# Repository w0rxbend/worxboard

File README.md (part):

<div align="center">

# ⌨️ worxboard

**An ErgoDox-style split keyboard, generated from one layout package.**

On-board RP2040 · ZMK wired split · a memory LCD on each half · per-key RGB · USB-C on both halves · MX hot-swap, fully assembled at JLCPCB or PCBWay · CNC aluminium case

<sub>🚧 <b>rev B is designed on four layers and its gates passed locally on 2026-11-12. Order only from a commit with a green pcb workflow. Not built.</b></sub>

    <br>

**[🌐 Live 3D viewer](https://w0rxbend.github.io/worxboard/) · [🛒 Order it](#-order-it) · [🚀 Zero to typing](#-from-zero-to-typing) · [🔧 Build guide](docs/buildguide_en.md) · [📋 BOM](docs/bom.md) · [🧾 Shopping list](docs/shopping-list.md)**<br>**[💾 Firmware](docs/firmware.md) · [🧱 Case](docs/case.md) · [📐 Design spec](docs/design.md) · [🧪 Verification](docs/verification.md)**

<sub>🖥️ Both halves in the browser 3D viewer, built from <a href="layout/build/layout.json">layout.json</a>: ErgoDox stagger, 25° thumbs, the display in the inner top slot, the tent legs. A render, not a photo, committed on 2026-11-02, before case revisions A3 to A5 and before rev B, so the case has no raised display bezel yet and the boards have no LEDs.</sub>

</div>

worxboard keeps the exact ErgoDox key positions and the 25° six-key thumb cluster. On each half, the top key of the inner column is replaced by a vertical memory LCD, an RGB LED sits under every switch, and the two halves link over TRRS with ZMK's wired split. Everything is generated from one layout package, [`layout/`](layout/): the KiCad schematics and PCBs, the build123d case, the ZMK physical layout, the docs tables and the 3D viewer. On every push to `main` and every pull request, CI rebuilds and checks the layout, the firmware, both PCBs with their order packages, and the case with its order package. The generated docs tables are checked by `just docs-check`, and the viewer is built by `just site`. Both also run in the manual `pages` workflow.

> [!WARNING]
> **Status: rev B passed its gates locally and in CI on 2026-11-12, and is tagged as the pre-release `v0.2.0-revB`; only the order-day stock check stays open.** Its PCBs moved to four layers (solid GND and VLED planes, scripted LED cells, the repo's own maze router; no Freerouting, [REVB-8](docs/deviations.md)), and the results of the final routed boards are in [verification.md](docs/verification.md#rev-b-results). Rev B puts an SK6812MINI-E RGB LED under every switch, moves the display 1.0 mm back from the C6R1 key well, folds in the pre-order review's minor points and adds a PCBWay order package beside the JLCPCB one ([deviations REVB-1 to REVB-9](docs/deviations.md#revb-rev-b-per-key-rgb-display-setback-and-review-fixes-layout-pcb-firmware-case-docs)). [verification.md](docs/verification.md) records rev A's gates **G1–G3** as passed and the rev B gates with their results. No board of either revision has been made, and nothing has been tested on hardware. Do not order assembled rev B boards until the `pcb` workflow is green on the commit you order from and the stock check has run. The frozen rev A design is [`docs/design.md`](docs/design.md), and every change from it is listed in [`docs/deviations.md`](docs/deviations.md). Read the [known open issues](#-known-open-issues) before you order.

| ⌨️ Keys | 🧠 MCU | 📟 Display | 🌈 RGB | 🔗 Split link | 🏭 Assembly | 🧱 Case |
|:-:|:-:|:-:|:-:|:-:|:-:|:-:|
| **74**, 37 per half | **RP2040** on each PCB | **160 × 68** memory LCD per half | **37** SK6812MINI-E per half, one under each switch | **115 200** baud UART over TRRS | **201** fab-assembled parts per half | **≈ 349 g** of 6061-T6 per half |

<details>
<summary>🚦 Status by part</summary>

| Part | State |
|---|---|
| 🧬 Layout (`layout/`) | ✅ **Done.** Keys, thumbs, display, LED positions and chain, jacks, holes, outline, zones and the GPIO map; checked by `just layout-check` |
| 🟩 PCB (`pcb/`) | ✅ **Designed (rev B, four layers). Gates passed locally and in CI; the stock check is open until the order day.** Both halves are generated in KiCad 10, with the per-key RGB chain, the VLED switch U6 and the data buffer U7, on F.Cu / GND plane / VLED plane / B.Cu. The gates of the final routed boards and their order packages in [`pcb/production/`](pcb/production/) are recorded in [verification.md](docs/verification.md#rev-b-results). The pipeline stops on an ERC error, a netlist mismatch (the RGB chain included), a DRC violation, an unconnected item or a parity issue, and on a failed scripted check: the USB pair, crystal, decoupling, U1 ground return and GND links, via-in-pad, J1 pin-in-paste, outline, and each LED in its switch window. |
| 💾 Firmware (`firmware/`, `zephyr/`, `build.yaml`) | 🔨 **Builds.** All six `build.yaml` rows build locally and in CI: left central, right peripheral, two role-swap rows and two RP2350A rows. Both screens are laid out portrait for the upright display. The LED chains run as ZMK underglow, capped at 8 % brightness. Nothing has run on hardware. |
| 🧱 Case and plates (`case/`, `plates/`) | ✅ **Orderable.** Every case check passes, and so does JLCCNC's internal-corner rule. `just fitcheck` reports 0 mm³ of interference against both PCB STEPs plus the layout envelopes. The JLCCNC / JLC3DP package for case revision A5 (with PCBWay notes) is committed in [`case/production/`](case/production/README.md). Nothing has been printed or machined. |
| 📚 Docs and microsite (`docs/`, `site/`) | ✅ **Done.** The turnkey ordering guides for JLCPCB and PCBWay, shopping list, build guide, generated BOM, pinout and matrix, and the electrical, case, legs and firmware docs. The site is a product page with the 3D viewer and a build guide rendered from these docs. |
| 🧪 Gates and release | ✅ **Rev A and rev B passed. Rev B is the pre-release `v0.2.0-revB`.** [`docs/verification.md`](docs/verification.md) records rev A's integration tests (111 passed), CI, order-package checks and gates G1–G3, and the rev B gate results of 2026-11-12. [`release.yml`](.github/workflows/release.yml) publishes the committed order packages, the firmware and the case files on a `v*` tag. The tag `v0.1.0-revA` points at the rev A commit, `v0.2.0-revB` at rev B. |
| 🛠️ Hardware | ⏳ **Not built.** What only a real board can confirm is [listed](docs/verification.md#not-verified-until-a-board-is-built). |

</details>

## 🧭 Contents

| 👀 See it | 🛠️ Make it | 📖 Know it |
|---|---|---|
| [📸 Gallery](#-gallery) | [🚀 From zero to typing](#-from-zero-to-typing) | [🤖 Generated, not drawn](#-generated-not-drawn) |
| [✨ Features](#-features) | [🛒 Order it](#-order-it) | [🐛 Known open issues](#-known-open-issues) |
| [📊 Specs](#-specs) | [🔧 Build it](#-build-it) | [🔭 Future work](#-future-work) |
| [📐 Layout and matrix](#-layout-and-matrix) | [💾 Firmware](#-firmware) | [🌳 Repository layout](#-repository-layout) |
| [🌐 Spin it in your browser](#-spin-it-in-your-browser) | [🧱 Case](#-case) | [📚 Documentation](#-documentation) |
| | [🧰 Build from source](#-build-from-source) | [🙏 Credits](#-credits) |
| | [📦 Get the files](#-get-the-files) | [📜 License](#-license) |

## 📸 Gallery

> [!NOTE]
> Every image in this README is a render, a CAD drawing or a screenshot. No photos exist yet, because no board has been built. The PCB renders and the CPL proofs were regenerated from the rev B boards on 2026-11-12, and the case renders show case revision A5. The two viewer images were captured from the microsite's 3D viewer on 2026-11-12: they show rev B in the case of revision A5, with the LEDs lit. KiCad has no 3D model for the USB-C, the TRRS jack or the hot-swap sockets, so the PCB renders show only their footprints.

<table>
<tr><td align="center" width="50%"><br><sub>💥 Right half exploded in the viewer: tray, PCB, printed spacer, top shell, switches, keycaps</sub></td><td align="center" width="50%"><br><sub>🦵 Closed right-half case with its three custom tent legs (CAD render)</sub></td></tr>
<tr><td align="center"><br><sub>🟩 Left PCB, top (rev B): RP2040, flash, USB-C J1, BOOT/RESET, JP1 (“cut = split power”), display socket J3, TRRS jack J2 on the inner bump</sub></td><td align="center"><br><sub>🟩 Right PCB, top (rev B): mirrored, same netlist; both boards print DO NOT HOT-PLUG TRRS and HOST → LEFT by J2</sub></td></tr>
<tr><td align="center"><br><sub>🟩 Left PCB, bottom (rev B): 37 hot-swap socket footprints and 37 diodes; rev B adds an LED and its cap at every key</sub></td><td align="center"><br><sub>🟩 Right PCB, bottom (rev B): 37 socket footprints and 37 diodes, all fitted by the fab</sub></td></tr>
<tr><td align="center" colspan="2"><br><sub>🧱 Both CNC top shells: the plate is milled into the key well, with 2u stabiliser cut-outs and a display window on each half</sub></td></tr>
</table>

## ✨ Features

<table>
<tr><td width="33%" valign="top">

**📐 Exact ErgoDox layout**<br>The switch centres, the column stagger and the 25° thumb cluster come from the original ErgoDox PCB. The thumb keys match it within 0.002 mm, and the main keys match the spec table within 0.0001 mm. 37 keys per half, 74 in total.

</td><td width="33%" valign="top">

**📟 A display on each half**<br>A Sharp LS011B7DH03 memory LCD (160 × 68) on a nice!view-class module sits where the inner top key was, behind a window in the case. The left half shows the ZMK status screen. The right half shows a custom lock-indicator screen.

</td><td width="33%" valign="top">

**🧠 On-board RP2040**<br>There is no controller daughterboard. The support circuit is derived from the [Corne v4.1](https://github.com/foostan/crkbd): QSPI flash, a 12 MHz crystal, an LDO and ESD arrays. JLCPCB or PCBWay fits all 201 parts per half, on both sides.

</td></tr>
<tr><td valign="top">

**🔌 USB-C on both halves**<br>Plug the host into the **left** half. The right USB-C gives power and UF2 flashing. Schottky diodes let you plug in both at once without back-feeding either host.

</td><td valign="top">

**🔗 A careful wired split**<br>ZMK `zmk,wired-split` runs on UART0 at 115 200 baud over a straight TRRS cable. The tip carries only 1 kΩ-limited data. Power sits on Ring2 behind a 250 mA polyfuse, and solder jumper JP1 turns cable power off.

</td><td valign="top">

**🔥 Hot-swap, no PCB soldering**<br>MX hot-swap sockets of the CPG151101S11 type sit on the bottom, with 2u plate-mount stabilisers on two thumb keys per half. The fab fits every PCB part, display socket and LEDs included; you solder only the displays' header pins (and any J1 shell leg that arrives bare).

</td></tr>
<tr><td valign="top">

**🧱 CNC aluminium case**<br>Each half has a 6061-T6 top shell with the 1.5 mm plate milled into it, a 6061-T6 tray and a printed 3 mm spacer. The finish is bead blast plus anodize. A raised bezel covers the display.

</td><td valign="top">

**🦵 Tent legs like the EZ**<br>Each half has three mounts at the stock ErgoDox EZ positions. Every mount takes one custom aluminium leg with a TPU foot cap, clamped by an M3 × 12 collarless thumbscrew and a friction washer.

</td><td valign="top">

**🤖 Generated, not drawn**<br>The schematic, placement, routing, DRC, fab files, case, physical layout and docs tables are all scripts. The PCB stages run headless in a digest-pinned KiCad container, with the repo's own router and seeded ids, so a rebuild gives byte-identical boards.

</td></tr>
<tr><td colspan="3" valign="top">

**🌈 Per-key RGB (rev B)**<br>An SK6812MINI-E sits under every switch, 37 per half, reverse-mounted in a cutout so it shines up through the switch's LED window on the south side (towards you); the fab places them with everything else. ZMK drives each half's chain as an underglow strip: whole-board effects (solid, breathe, spectrum, swirl), toggle, hue and brightness on the layer-1 thumbs, and the left half relays them to the right. There are no per-key or per-layer colours. A load switch keeps the LEDs unpowered until the firmware turns them on, and brightness is capped at 8 % so that one cable can feed both halves. None of it has run on hardware yet.

</td></tr>
</table>

## 📊 Specs

| Spec | rev B |
|---|---|
| ⌨️ **Keys** | 74 (37 per half). Each half has a 6 × 7 `col2row` matrix; ZMK sees one 6 × 14 transform |
| 🧠 **Controller** | RP2040 (QFN-56) per half, with W25Q128JVSIQ 16 MB QSPI flash and a 12 MHz crystal |
| 📟 **Display** | Sharp LS011B7DH03, 160 × 68 memory LCD on a nice!view-class module, driven over PIO1 SPI at 1 MHz. Rev B sets the module 1.0 mm back, so its far end stops about 0.2–0.3 mm short of the C6R1 key well (36 mm module plus its V-cut) |
| 🌈 **RGB** | 37 SK6812MINI-E per half, reverse-mounted on the bottom under each switch, facing south. One chain per half: GP22 through a buffer (U7) on PIO0; VLED switched from VSYS by U6 on GP23, limited to 0.45 A. ZMK underglow effects, brightness capped at 8 % |
| 🔗 **Split link** | 3.5 mm TRRS, ZMK wired split on UART0 at 115 200 baud, full duplex |
| 🔌 **USB** | USB-C 2.0 full speed on both halves (HRO TYPE-C-31-M-12); the host goes on the left |
| 🟩 **PCB** | 4 layers (signal, GND plane, VLED plane, signal), 1.6 mm FR4, 1 oz outer / 0.5 oz inner copper, ENIG, 182.84 × 158.75 mm per half. The fab places 201 parts per half: 53 on top, and 148 on the bottom (37 sockets, 37 diodes, 37 LEDs and their 37 caps) |
| 🎹 **Switches** | 74 MX-compatible plate-mount switches, 3- or 5-pin, in hot-swap sockets; 4 × 2u plate-mount stabilisers |
| 💾 **Firmware** | ZMK, HWMv2 board `worxbend/worxboard`, pinned at `4dd95d78`; ZMK Studio on the left central |
| 🧱 **Case** | 3 parts per half (CNC top and tray, printed spacer); 192.4 × 165.6 × 17.6 mm, 19.6 mm at the display bezel; about 349 g per half |
| 🦵 **Legs** | 3 per half, held by M3 × 12 DIN 653 thumbscrews with friction washers |

<details>
<summary>🔬 Full specs: key parts, power path, TRRS contacts, GPIO map</summary>

**🧩 Key parts per half** (the full generated table is in [docs/bom.md](docs/bom.md)):

| Ref | Part | LCSC | Ref | Part | LCSC |
|---|---|---|---|---|---|
| U1 | RP2040, QFN-56 | [C2040](https://jlcpcb.com/partdetail/C2040) | U2 | W25Q128JVSIQ, 16 MB QSPI flash | [C97521](https://jlcpcb.com/partdetail/C97521) |
| Y1 | 12 MHz 3225 crystal, YXC XL2EL89CRI-111YLC-12M | [C49304726](https://jlcpcb.com/partdetail/C49304726) | U3 | AP2112K-3.3, 600 mA LDO | [C51118](https://jlcpcb.com/partdetail/C51118) |
| U4, U5 | USBLC6-2SC6 ESD arrays (USB, TRRS) | [C7519](https://jlcpcb.com/partdetail/C7519) | D1 | B5819W, 1 A Schottky | [C8598](https://jlcpcb.com/partdetail/C8598) |
| F1 | nSMD025-24V PTC, 250 mA hold | [C70069](https://jlcpcb.com/partdetail/C70069) | J1 | HRO TYPE-C-31-M-12 USB-C receptacle | [C165948](https://jlcpcb.com/partdetail/C165948) |
| J2 | PJ-320D-4A TRRS jack, SMD | [C95562](https://jlcpcb.com/partdetail/C95562) | J3 | 1×5 2.54 mm female socket, 5.0 mm tall (the only through-hole part) | [C27985230](https://jlcpcb.com/partdetail/C27985230) |
| SW1, SW2 | TS-1088R tact switches (BOOT, RESET) | [C455280](https://jlcpcb.com/partdetail/C455280) | SK101–SK137 | MX hot-swap socket, HanElectricity CPG151101S11-16 | [C41430893](https://jlcpcb.com/partdetail/C41430893) |
| D101–D137 | 1N4148W matrix diodes | [C81598](https://jlcpcb.com/partdetail/C81598) | LED101–LED137 | SK6812MINI-E RGB LED, reverse mount (rev B) | [C5149201](https://jlcpcb.com/partdetail/C5149201) |
| U6 | SY6280AAC load switch, VSYS → VLED (rev B) | [C55136](https://jlcpcb.com/partdetail/C55136) | U7 | SN74LV1T34DBVR buffer, GP22 → LED101 (rev B) | [C100024](https://jlcpcb.com/partdetail/C100024) |
| C1–C3 | 10 µF 0603 10 V X5R (rev B; was 0402 6.3 V) | [C19702](https://jlcpcb.com/partdetail/C19702) |  |  |  |

`design.py` fits 201 parts per half with 26 LCSC numbers; each side's [order README](pcb/production/left/README.md) gives the BOM and CPL line counts. The retired parts C2803348 (socket), C113767 (flash), C91749 (crystal) and C15525 (rev A's 0402 10 µF) fail `stock.py` and `netcmp.py` if they come back.

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
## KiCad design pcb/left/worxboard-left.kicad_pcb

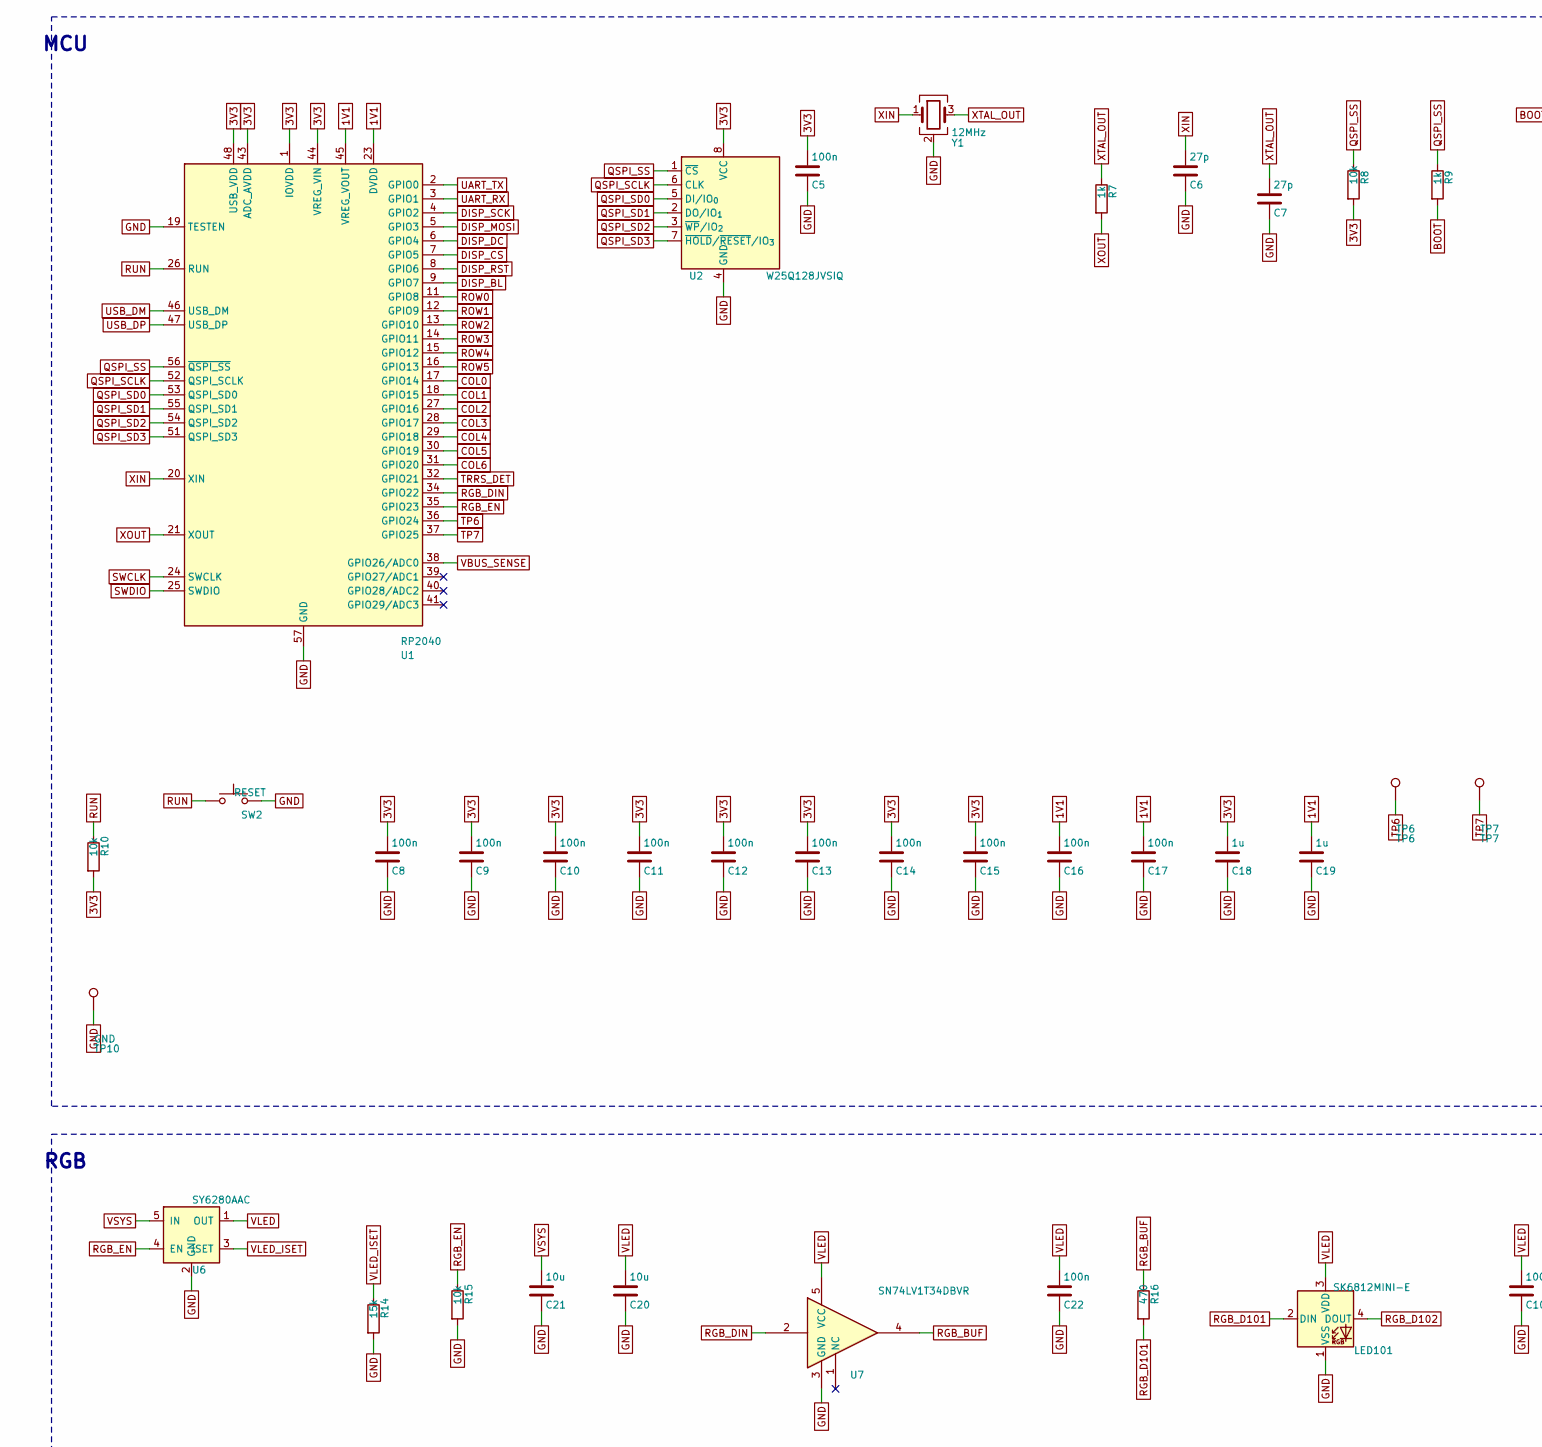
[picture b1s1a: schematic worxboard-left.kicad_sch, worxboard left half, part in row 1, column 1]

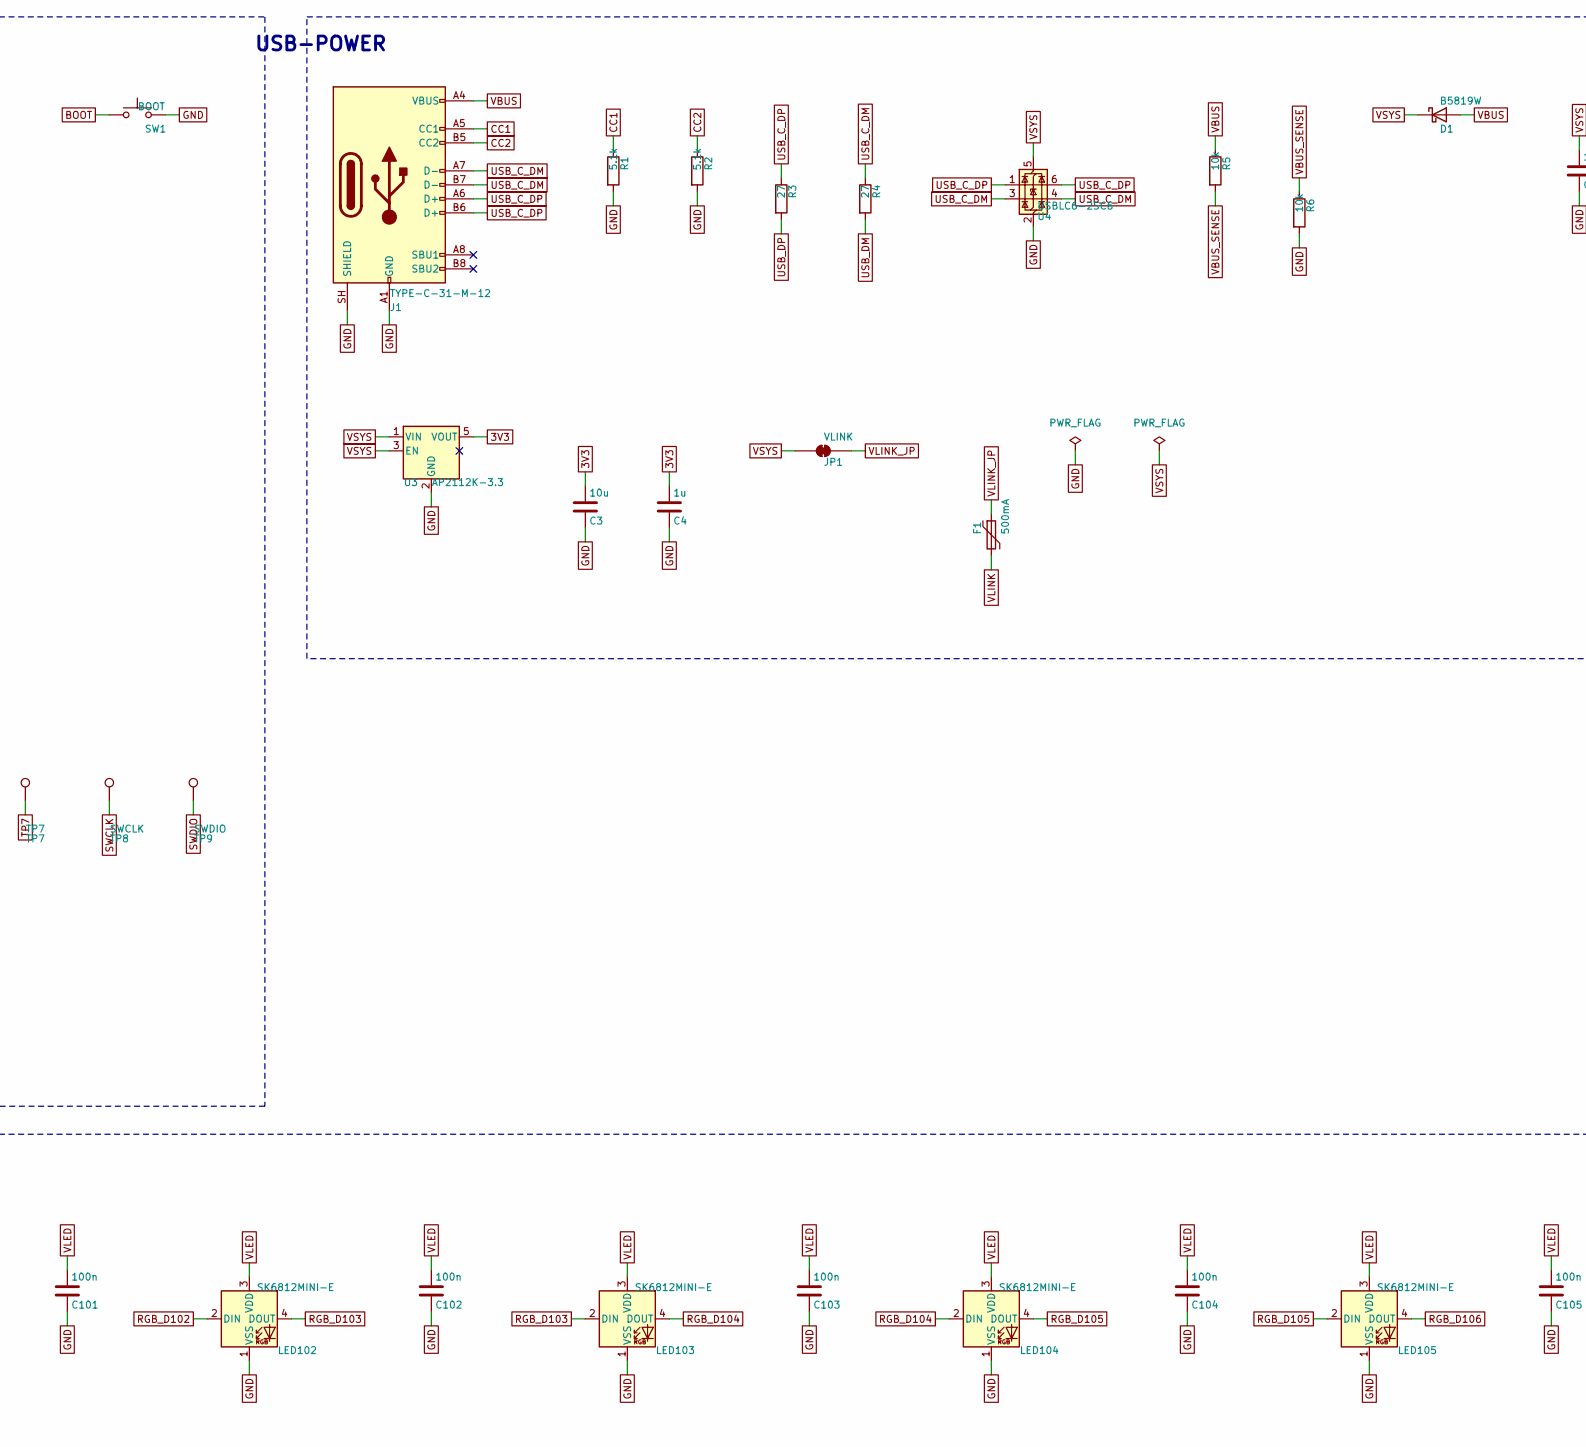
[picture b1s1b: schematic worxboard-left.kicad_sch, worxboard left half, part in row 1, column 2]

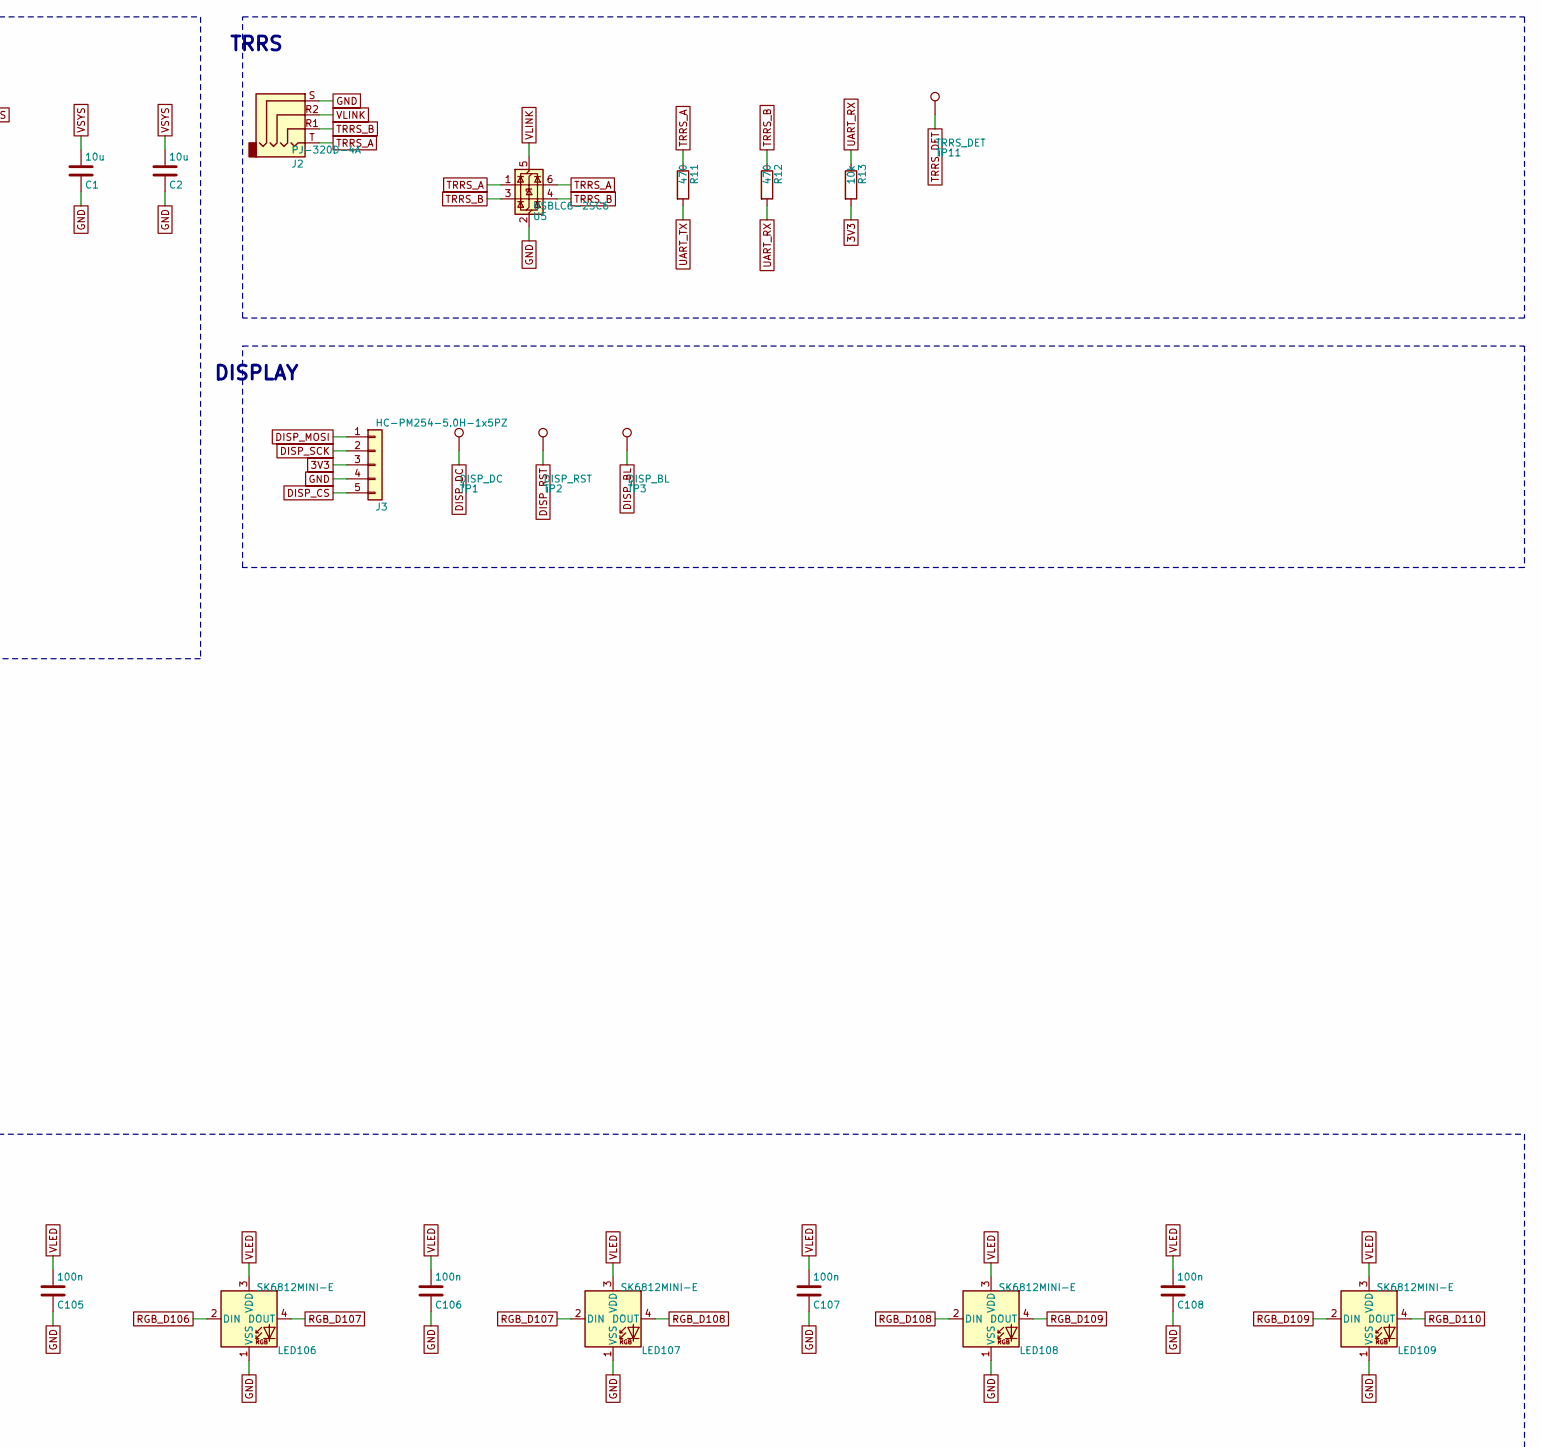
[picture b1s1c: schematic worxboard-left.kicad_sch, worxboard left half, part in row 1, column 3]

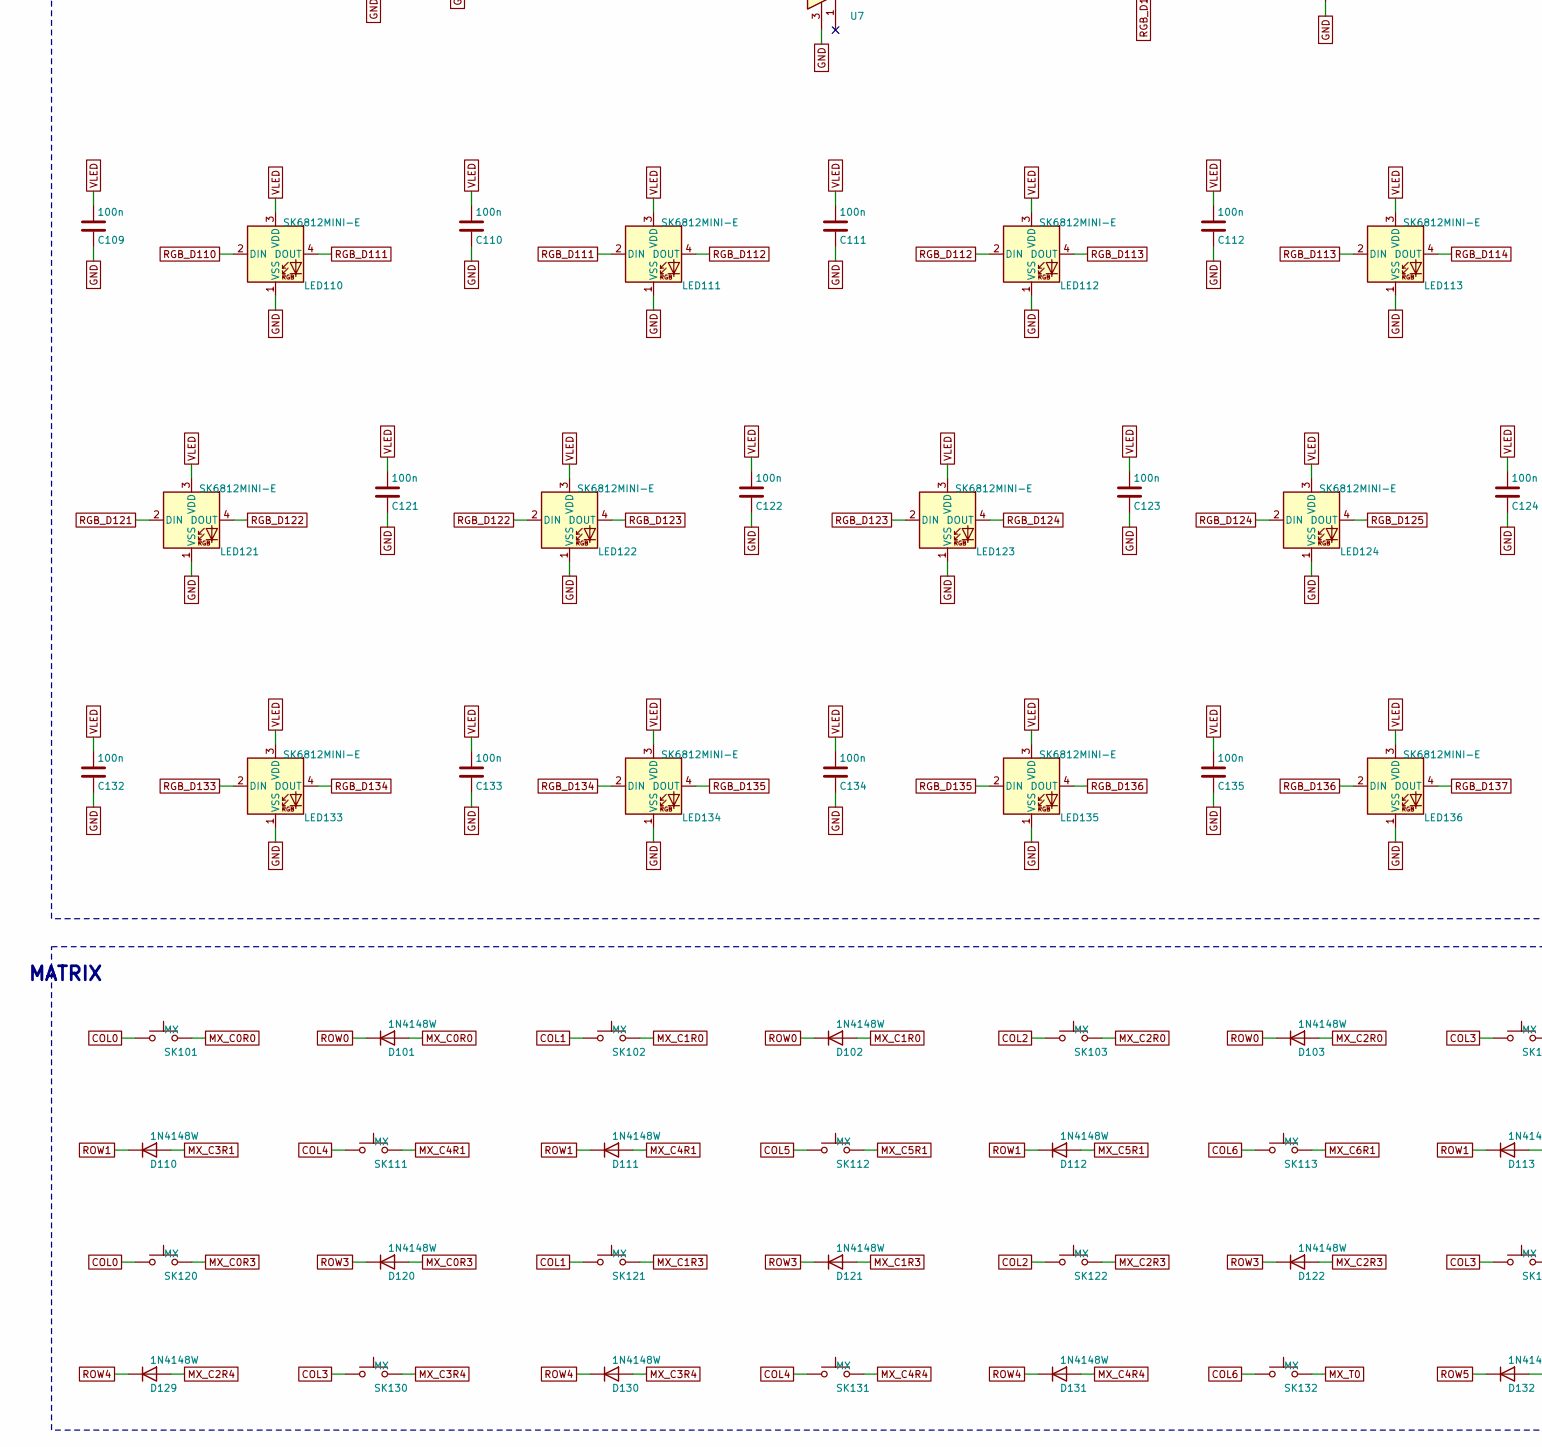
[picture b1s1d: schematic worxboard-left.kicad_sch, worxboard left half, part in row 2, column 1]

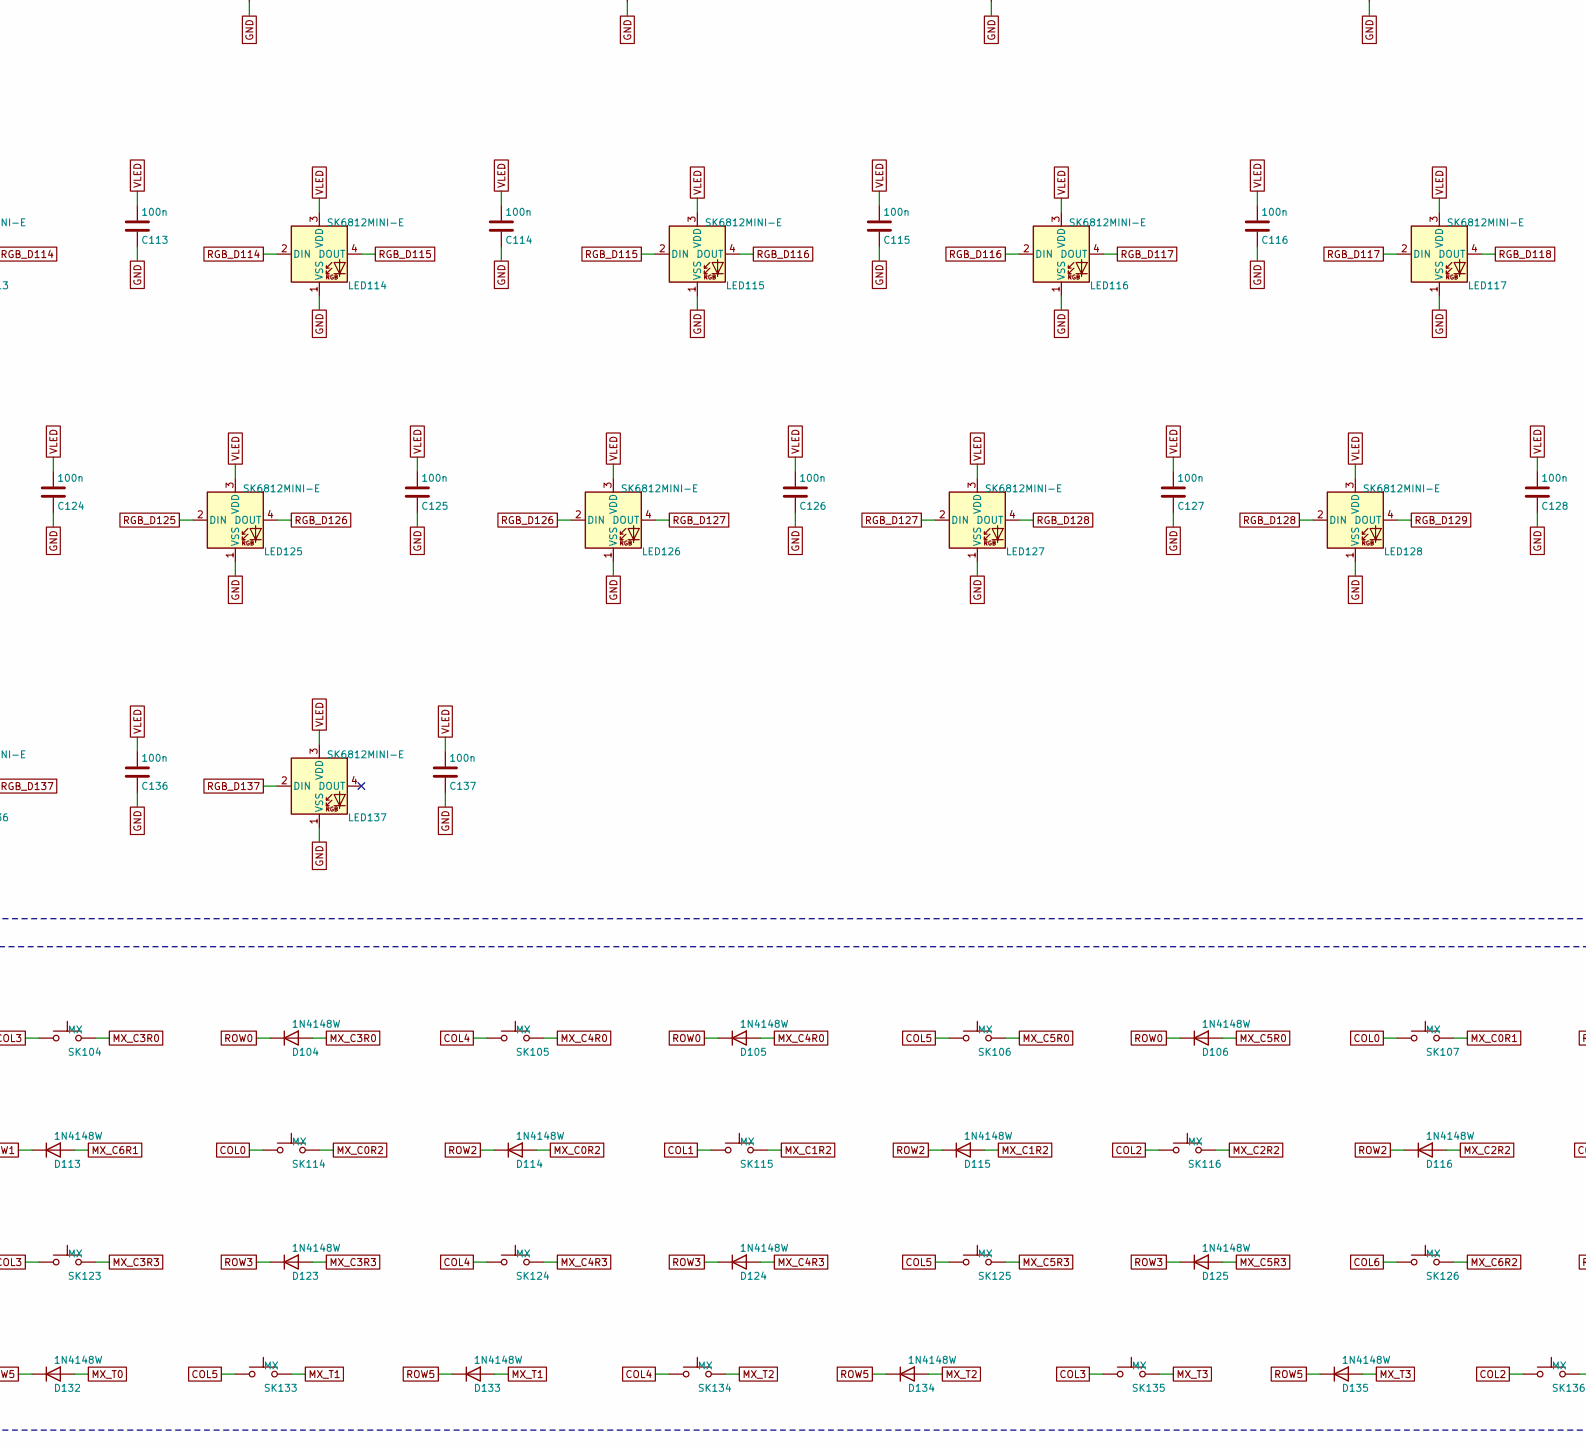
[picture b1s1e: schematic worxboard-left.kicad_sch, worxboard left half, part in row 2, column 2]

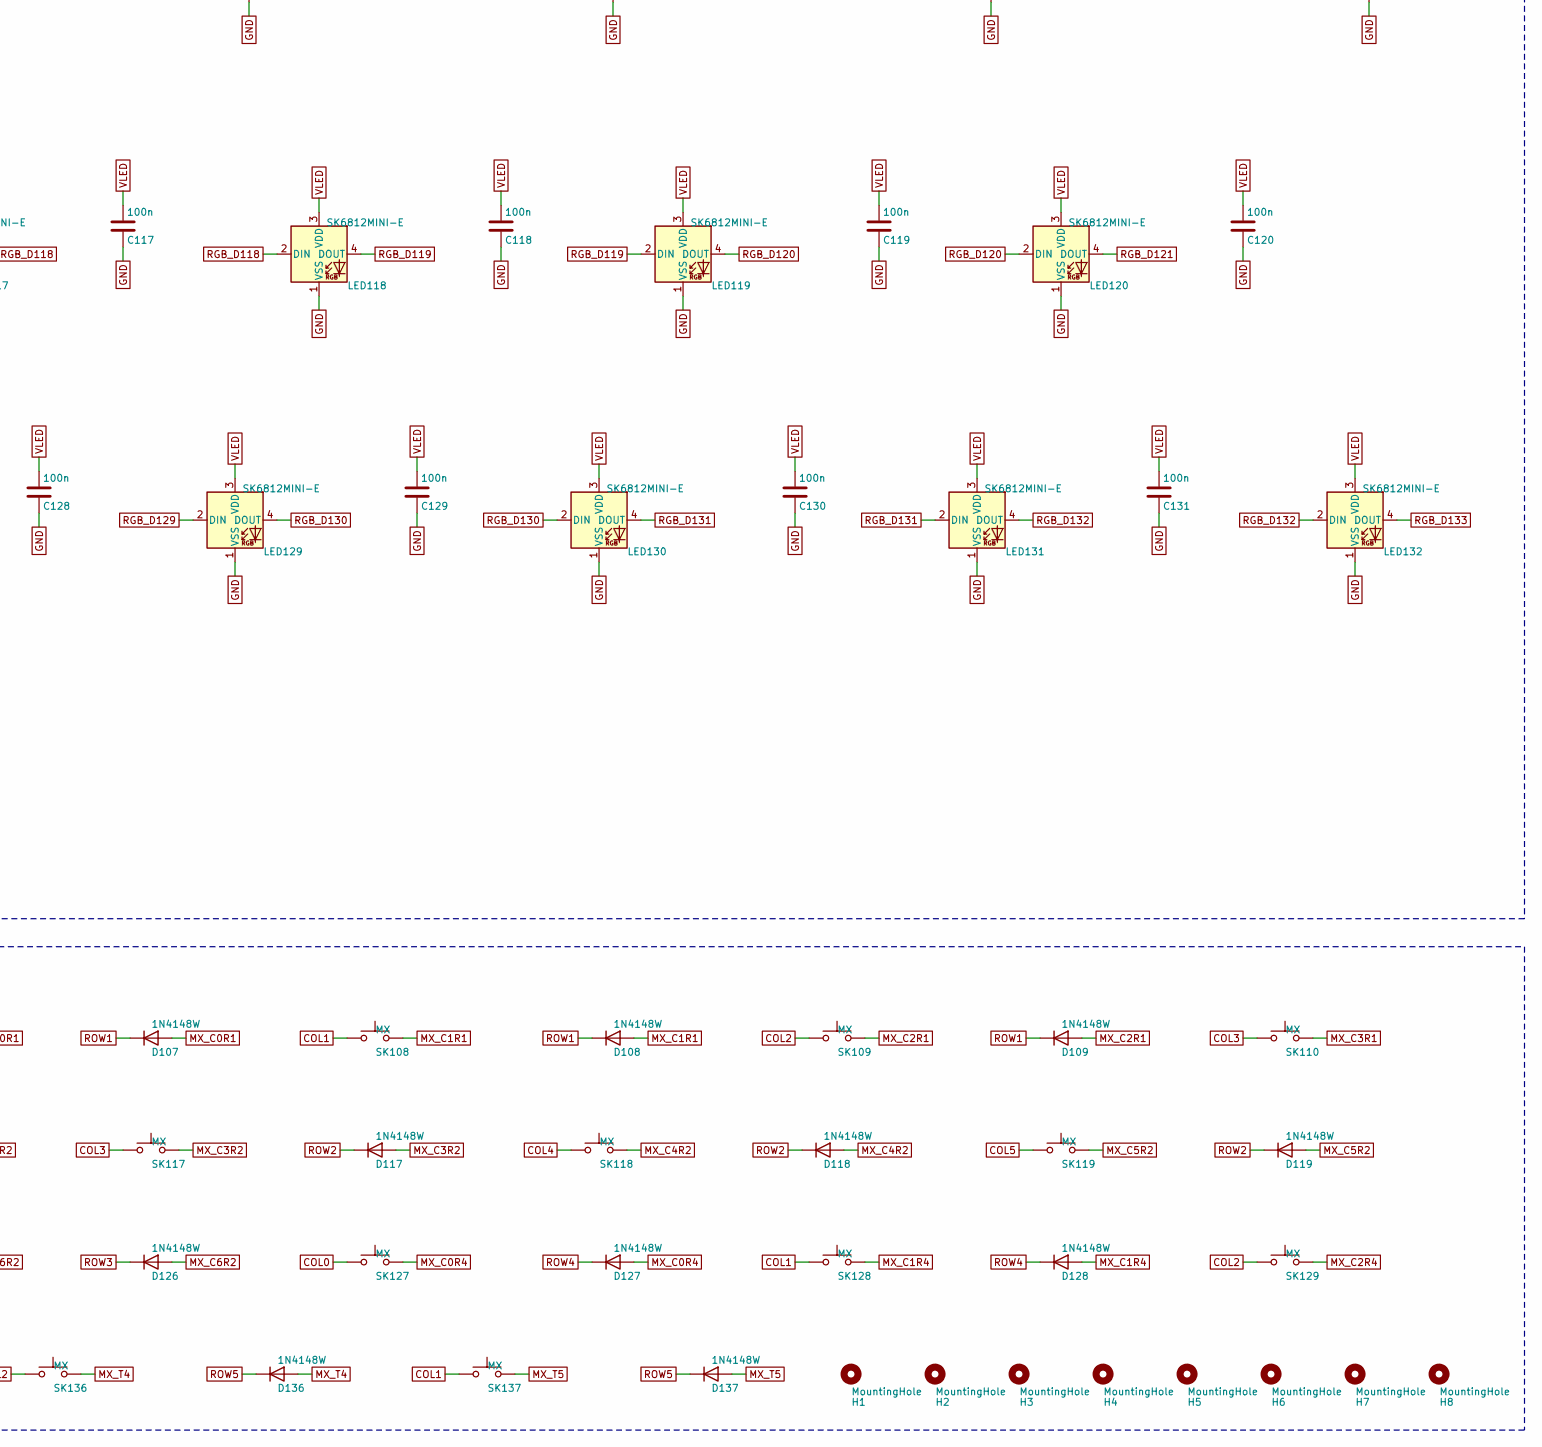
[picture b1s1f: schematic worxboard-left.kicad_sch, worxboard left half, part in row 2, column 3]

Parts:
C1, C2, C3, C20, C21: 10u; C_0603_1608Metric; LCSC C19702
C4, C18, C19: 1u; C_0402_1005Metric; LCSC C52923
C5, C8, C9, C10, C11, C12, C13, C14, C15, C16, C17, C22, C101, C102, C103, C104, C105, C106, C107, C108, C109, C110, C111, C112, C113, C114, C115, C116, C117, C118, C119, C120, C121, C122, C123, C124, C125, C126, C127, C128, C129, C130, C131, C132, C133, C134, C135, C136, C137: 100n; C_0402_1005Metric; LCSC C1525
C6, C7: 27p; C_0402_1005Metric; LCSC C1557
D1: B5819W; D_SOD-123; LCSC C8598
D101, D102, D103, D104, D105, D106, D107, D108, D109, D110, D111, D112, D113, D114, D115, D116, D117, D118, D119, D120, D121, D122, D123, D124, D125, D126, D127, D128, D129, D130, D131, D132, D133, D134, D135, D136, D137: 1N4148W; D_SOD-123; LCSC C81598
F1: 500mA; Fuse_1206_3216Metric; LCSC C70076
H1, H2, H3, H4, H5, H6, H7, H8: MountingHole; MountingHole_2.7mm_M2.5
J1: TYPE-C-31-M-12; USB_C_Receptacle_HRO_TYPE-C-31-M-12; LCSC C165948
J2: PJ-320D-4A; Jack_3.5mm_PJ320D_Horizontal; LCSC C95562
J3: HC-PM254-5.0H-1x5PZ; PinSocket_1x05_P2.54mm_Vertical_H5.0mm; LCSC C27985230
JP1: VLINK; SolderJumper-2_P1.3mm_Bridged_RoundedPad1.0x1.5mm
LED101, LED102, LED103, LED104, LED105, LED106, LED107, LED108, LED109, LED110, LED111, LED112, LED113, LED114, LED115, LED116, LED117, LED118, LED119, LED120, LED121, LED122, LED123, LED124, LED125, LED126, LED127, LED128, LED129, LED130, LED131, LED132, LED133, LED134, LED135, LED136, LED137: SK6812MINI-E; LED_SK6812MINI-E_ReverseMount; LCSC C5149201
R1, R2: 5.1k; R_0402_1005Metric; LCSC C25905
R3, R4: 27; R_0402_1005Metric; LCSC C2909343
R5, R6, R8, R10, R13, R15: 10k; R_0402_1005Metric; LCSC C25744
R7, R9: 1k; R_0402_1005Metric; LCSC C11702
R11, R12, R16: 470; R_0402_1005Metric; LCSC C25117
R14: 15k; R_0402_1005Metric; LCSC C25756
SK101, SK102, SK103, SK104, SK105, SK106, SK107, SK108, SK109, SK110, SK111, SK112, SK113, SK114, SK115, SK116, SK117, SK118, SK119, SK120, SK121, SK122, SK123, SK124, SK125, SK126, SK127, SK128, SK129, SK130, SK131, SK132, SK133, SK134, SK135, SK136, SK137: MX; SW_MX_Hotswap_Kailh; LCSC C41430893
SW1: BOOT; SW_SPST_TS-1088-xR020; LCSC C455280
SW2: RESET; SW_SPST_TS-1088-xR020; LCSC C455280
TP1: DISP_DC; TestPoint_Pad_D1.0mm
TP2: DISP_RST; TestPoint_Pad_D1.0mm
TP3: DISP_BL; TestPoint_Pad_D1.0mm
TP6: TP6; TestPoint_Pad_D1.0mm
TP7: TP7; TestPoint_Pad_D1.0mm
TP8: SWCLK; TestPoint_Pad_D1.0mm
TP9: SWDIO; TestPoint_Pad_D1.0mm
TP10: GND; TestPoint_Pad_D1.0mm
TP11: TRRS_DET; TestPoint_Pad_D1.0mm
U1: RP2040; QFN-56-1EP_7x7mm_P0.4mm_EP3.2x3.2mm; LCSC C2040
U2: W25Q128JVSIQ; SOIC-8_5.3x5.3mm_P1.27mm; LCSC C97521
U3: AP2112K-3.3; SOT-23-5; LCSC C51118
U4, U5: USBLC6-2SC6; SOT-23-6; LCSC C7519
U6: SY6280AAC; SOT-23-5; LCSC C55136
U7: SN74LV1T34DBVR; SOT-23-5; LCSC C100024
Y1: 12MHz; Crystal_SMD_3225-4Pin_3.2x2.5mm; LCSC C49304726

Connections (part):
1V1: C16.1, C17.1, C19.1, U1.23 (DVDD), U1.45 (VREG_VOUT), U1.50 (DVDD)
3V3: C3.1, C4.1, C5.1, C8.1, C9.1, C10.1, C11.1, C12.1, C13.1, C14.1, C15.1, C18.1, J3.3, R8.2, R10.2, R13.2, U1.1 (IOVDD), U1.10 (IOVDD), U1.22 (IOVDD), U1.33 (IOVDD), U1.42 (IOVDD), U1.43 (ADC_AVDD), U1.44 (VREG_VIN), U1.48 (USB_VDD), U1.49 (IOVDD), U2.8 (VCC), U3.5 (VOUT)
BOOT: R9.2, SW1.1
CC1: J1.A5 (CC1), R1.1
CC2: J1.B5 (CC2), R2.1
COL0: SK101.1, SK107.1, SK114.1, SK120.1, SK127.1, U1.17 (GPIO14)
COL1: SK102.1, SK108.1, SK115.1, SK121.1, SK128.1, SK137.1, U1.18 (GPIO15)
COL2: SK103.1, SK109.1, SK116.1, SK122.1, SK129.1, SK136.1, U1.27 (GPIO16)
COL3: SK104.1, SK110.1, SK117.1, SK123.1, SK130.1, SK135.1, U1.28 (GPIO17)
COL4: SK105.1, SK111.1, SK118.1, SK124.1, SK131.1, SK134.1, U1.29 (GPIO18)
COL5: SK106.1, SK112.1, SK119.1, SK125.1, SK133.1, U1.30 (GPIO19)
COL6: SK113.1, SK126.1, SK132.1, U1.31 (GPIO20)
DISP_BL: TP3.1, U1.9 (GPIO7)
DISP_CS: J3.5, U1.7 (GPIO5)
DISP_DC: TP1.1, U1.6 (GPIO4)
DISP_MOSI: J3.1, U1.5 (GPIO3)
DISP_RST: TP2.1, U1.8 (GPIO6)
DISP_SCK: J3.2, U1.4 (GPIO2)
GND: C1.2, C2.2, C3.2, C4.2, C5.2, C6.2, C7.2, C8.2, C9.2, C10.2, C11.2, C12.2, C13.2, C14.2, C15.2, C16.2, C17.2, C18.2, C19.2, C20.2, C21.2, C22.2, C101.2, C102.2, C103.2, C104.2, C105.2, C106.2, C107.2, C108.2, C109.2, C110.2, C111.2, C112.2, C113.2, C114.2, C115.2, C116.2, C117.2, C118.2, C119.2, C120.2, C121.2, C122.2, C123.2, C124.2, C125.2, C126.2, C127.2, C128.2, C129.2, C130.2, C131.2, C132.2, C133.2, C134.2, C135.2, C136.2, C137.2, J1.A1 (GND), J1.A12 (GND), J1.B1 (GND), J1.B12 (GND), J1.SH (SHIELD), J2.S, J3.4, LED101.1 (VSS), LED102.1 (VSS), LED103.1 (VSS), LED104.1 (VSS), LED105.1 (VSS), LED106.1 (VSS), LED107.1 (VSS), LED108.1 (VSS), LED109.1 (VSS), LED110.1 (VSS), LED111.1 (VSS), LED112.1 (VSS), LED113.1 (VSS), LED114.1 (VSS), LED115.1 (VSS), LED116.1 (VSS), LED117.1 (VSS), LED118.1 (VSS)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
MX_C0R0: D101.2 (A), SK101.2
MX_C0R1: D107.2 (A), SK107.2
MX_C0R2: D114.2 (A), SK114.2
MX_C0R3: D120.2 (A), SK120.2
MX_C0R4: D127.2 (A), SK127.2
MX_C1R0: D102.2 (A), SK102.2
MX_C1R1: D108.2 (A), SK108.2
MX_C1R2: D115.2 (A), SK115.2
MX_C1R3: D121.2 (A), SK121.2
MX_C1R4: D128.2 (A), SK128.2
MX_C2R0: D103.2 (A), SK103.2
MX_C2R1: D109.2 (A), SK109.2
MX_C2R2: D116.2 (A), SK116.2
MX_C2R3: D122.2 (A), SK122.2
MX_C2R4: D129.2 (A), SK129.2
MX_C3R0: D104.2 (A), SK104.2
MX_C3R1: D110.2 (A), SK110.2
MX_C3R2: D117.2 (A), SK117.2
MX_C3R3: D123.2 (A), SK123.2
MX_C3R4: D130.2 (A), SK130.2
MX_C4R0: D105.2 (A), SK105.2
MX_C4R1: D111.2 (A), SK111.2
MX_C4R2: D118.2 (A), SK118.2
MX_C4R3: D124.2 (A), SK124.2
MX_C4R4: D131.2 (A), SK131.2
MX_C5R0: D106.2 (A), SK106.2
MX_C5R1: D112.2 (A), SK112.2
MX_C5R2: D119.2 (A), SK119.2
MX_C5R3: D125.2 (A), SK125.2
MX_C6R1: D113.2 (A), SK113.2
MX_C6R2: D126.2 (A), SK126.2
MX_T0: D132.2 (A), SK132.2
MX_T1: D133.2 (A), SK133.2
MX_T2: D134.2 (A), SK134.2
MX_T3: D135.2 (A), SK135.2
MX_T4: D136.2 (A), SK136.2
MX_T5: D137.2 (A), SK137.2
QSPI_SCLK: U1.52 (QSPI_SCLK), U2.6 (CLK)
QSPI_SD0: U1.53 (QSPI_SD0), U2.5 (DI/IO_{0})
QSPI_SD1: U1.55 (QSPI_SD1), U2.2 (DO/IO_{1})
QSPI_SD2: U1.54 (QSPI_SD2), U2.3 (~WP/IO_{2})
QSPI_SD3: U1.51 (QSPI_SD3), U2.7 (~HOLD/~RESET/IO_{3})
QSPI_SS: R8.1, R9.1, U1.56 (~QSPI_SS), U2.1 (~CS)
RGB_BUF: R16.1, U7.4
RGB_D101: LED101.2 (DIN), R16.2
RGB_D102: LED101.4 (DOUT), LED102.2 (DIN)
RGB_D103: LED102.4 (DOUT), LED103.2 (DIN)
RGB_D104: LED103.4 (DOUT), LED104.2 (DIN)
RGB_D105: LED104.4 (DOUT), LED105.2 (DIN)
RGB_D106: LED105.4 (DOUT), LED106.2 (DIN)
RGB_D107: LED106.4 (DOUT), LED107.2 (DIN)
RGB_D108: LED107.4 (DOUT), LED108.2 (DIN)
RGB_D109: LED108.4 (DOUT), LED109.2 (DIN)
RGB_D110: LED109.4 (DOUT), LED110.2 (DIN)
RGB_D111: LED110.4 (DOUT), LED111.2 (DIN)
RGB_D112: LED111.4 (DOUT), LED112.2 (DIN)
RGB_D113: LED112.4 (DOUT), LED113.2 (DIN)
RGB_D114: LED113.4 (DOUT), LED114.2 (DIN)
RGB_D115: LED114.4 (DOUT), LED115.2 (DIN)
RGB_D116: LED115.4 (DOUT), LED116.2 (DIN)
RGB_D117: LED116.4 (DOUT), LED117.2 (DIN)
RGB_D118: LED117.4 (DOUT), LED118.2 (DIN)
RGB_D119: LED118.4 (DOUT), LED119.2 (DIN)
RGB_D120: LED119.4 (DOUT), LED120.2 (DIN)
RGB_D121: LED120.4 (DOUT), LED121.2 (DIN)
RGB_D122: LED121.4 (DOUT), LED122.2 (DIN)
RGB_D123: LED122.4 (DOUT), LED123.2 (DIN)
RGB_D124: LED123.4 (DOUT), LED124.2 (DIN)
RGB_D125: LED124.4 (DOUT), LED125.2 (DIN)
RGB_D126: LED125.4 (DOUT), LED126.2 (DIN)
RGB_D127: LED126.4 (DOUT), LED127.2 (DIN)
RGB_D128: LED127.4 (DOUT), LED128.2 (DIN)
RGB_D129: LED128.4 (DOUT), LED129.2 (DIN)
RGB_D130: LED129.4 (DOUT), LED130.2 (DIN)
RGB_D131: LED130.4 (DOUT), LED131.2 (DIN)
RGB_D132: LED131.4 (DOUT), LED132.2 (DIN)
RGB_D133: LED132.4 (DOUT), LED133.2 (DIN)
RGB_D134: LED133.4 (DOUT), LED134.2 (DIN)
RGB_D135: LED134.4 (DOUT), LED135.2 (DIN)
RGB_D136: LED135.4 (DOUT), LED136.2 (DIN)
RGB_D137: LED136.4 (DOUT), LED137.2 (DIN)
RGB_DIN: U1.34 (GPIO22), U7.2
RGB_EN: R15.1, U1.35 (GPIO23), U6.4 (EN)
ROW0: D101.1 (K), D102.1 (K), D103.1 (K), D104.1 (K), D105.1 (K), D106.1 (K), U1.11 (GPIO8)
ROW1: D107.1 (K), D108.1 (K), D109.1 (K), D110.1 (K), D111.1 (K), D112.1 (K), D113.1 (K), U1.12 (GPIO9)
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
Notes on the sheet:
MCU
USB-POWER
TRRS
DISPLAY
RGB
MATRIX

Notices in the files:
README.md:
📜 License:
- Code (`layout/`, `pcb/scripts/`, `case/*.py`, `firmware/`, `tools/`, `site/`): [GPL-3.0](LICENSE). The ZMK board files under `firmware/zmk/boards/` carry ZMK's MIT licence in their SPDX headers.
- Hardware (`pcb/` KiCad files and libraries, case geometry outputs, `plates/`, `docs/`): [CERN-OHL-S-2.0](LICENSE-HARDWARE). **Maintainer to confirm** this split before the first hardware tag.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
License: GPL v3
License: CERN-OHL-S-2.0
The key and mounting-hole coordinates come from the original ErgoDox PCB by Fredrik Atmer and contributors (GPL-3.0).
